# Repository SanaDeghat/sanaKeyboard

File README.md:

# sanaKeyboard
What?
Its (then pcb of) my own custom keyboard. its a wireless split keyboard (in theory) that uses nice nano! 

Why?
So I havwe this firend who rly liked hardware and keeps talkign about it, plus i kinda bacame a stasis sidekick so i figured i should prob learn how to do hardware given that im like guiding ppl in it. That + I keep seeing vdieos of ppl going click click click on their fancy ahh mechanical keyboard and i cant efford that so i figured i make my own, that said im not printing it this was kind of my firs time so ill make a better one next time and make that one!!!!

How?
I used keycad and urgogen! for more details pls go to my journal! 

Live demo: 
Im ngl idk how to live demo this so ill just put some pics here (i drew the fox myself int he the cutest) : 

What you struggled with and what you learned?
I cried istg from things not connecting it looked like pasta from hwo messy it was (look at my commits and journal for more info) but lowky i mifht be in the cult now it was kinda fun connecting everyhting (and thank you kai for helping me)

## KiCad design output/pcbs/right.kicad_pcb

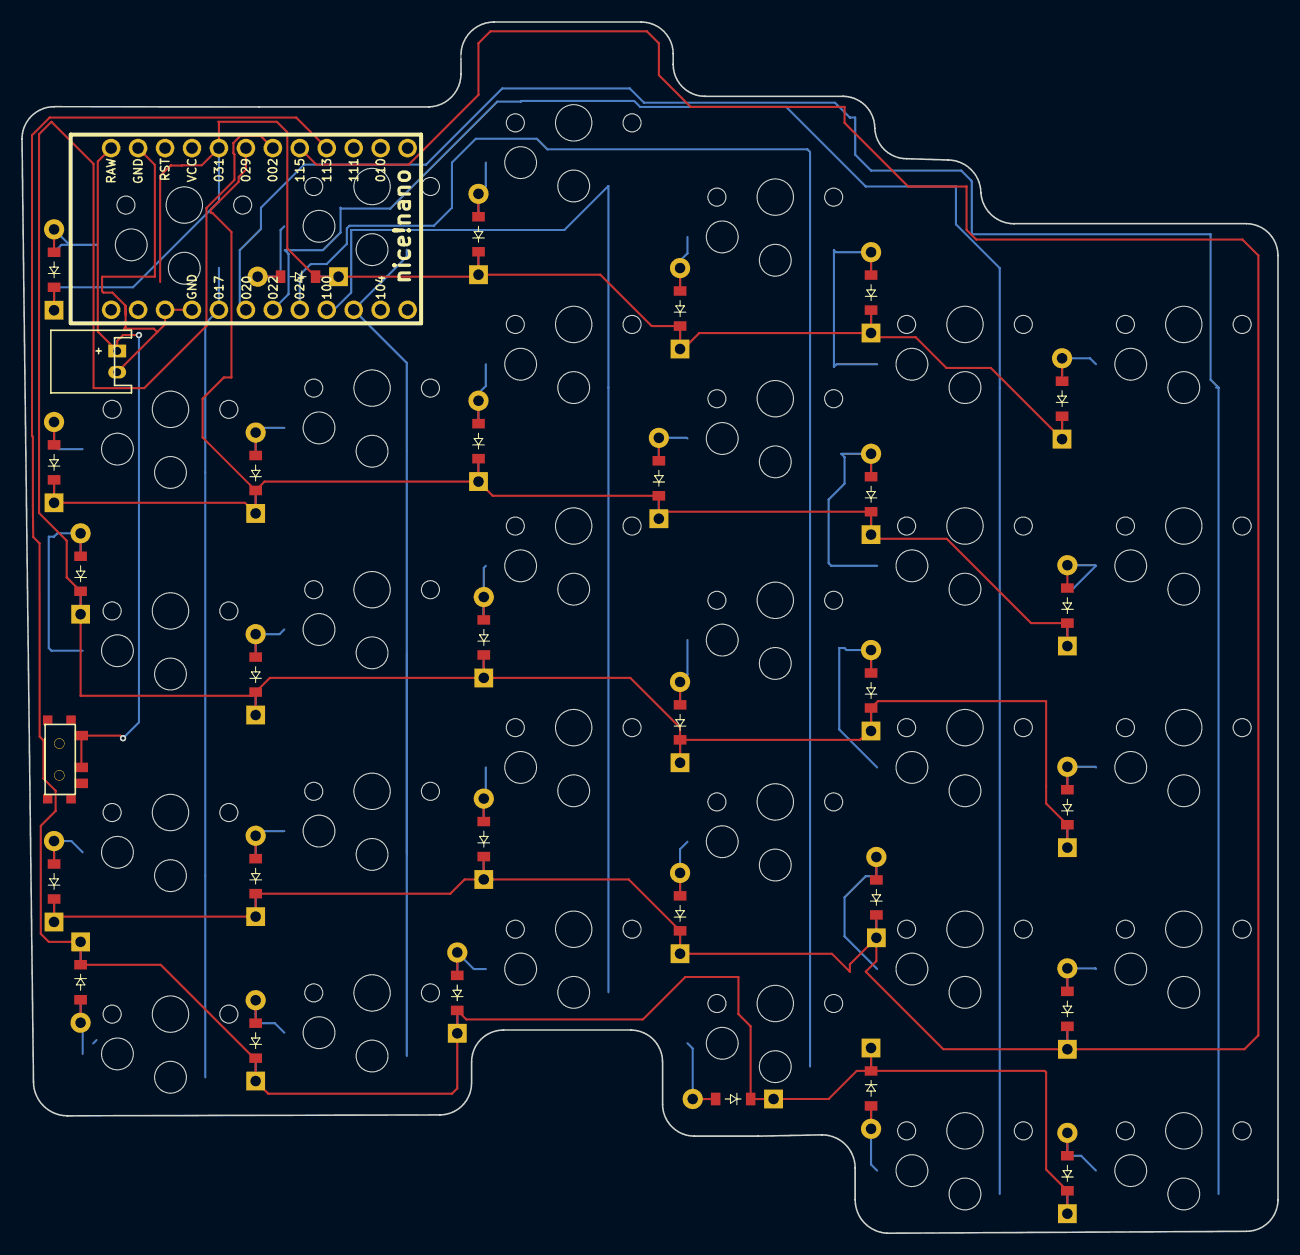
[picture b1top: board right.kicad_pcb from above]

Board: 2 copper layers, 118.4 x 114.2 mm, 63 parts (0 on the bottom side), 43 nets.

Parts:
D1, D2, D3, D4, D5, D6, D7, D8, D9, D10, D11, D12, D13, D14, D15, D16, D17, D18, D19, D20, D21, D22, D23, D24, D25, D26, D27, D28, D29, D30: ComboDiode
JST1: JST_PH_S2B-PH-K_02x2.00mm_Angled
MCU1: nice_nano
S1, S2, S3, S4, S5, S6, S7, S8, S9, S10, S11, S12, S13, S14, S15, S16, S17, S18, S19, S20, S21, S22, S23, S24, S25, S26, S27, S28, S29, S30: PG1350
T1: SPDT_C128955

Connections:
GND: JST1.2, MCU1.3, MCU1.4, MCU1.23
P002: D3.1, D8.1, D13.1, D18.1, D23.1, D28.1, MCU1.18
P011: MCU1.10, S21.1, S22.1, S23.1, S24.1, S25.1
P017: MCU1.5, S26.1, S27.1, S28.1, S29.1, S30.1
P020: MCU1.6, S1.1, S2.1, S3.1, S4.1, S5.1
P022: MCU1.7, S6.1, S7.1, S8.1, S9.1, S10.1
P024: MCU1.8, S11.1, S12.1, S13.1, S14.1, S15.1
P029: D4.1, D9.1, D14.1, D19.1, D24.1, D29.1, MCU1.19
P031: D5.1, D10.1, D15.1, D20.1, D25.1, D30.1, MCU1.20
P100: MCU1.9, S16.1, S17.1, S18.1, S19.1, S20.1
P113: D1.1, D6.1, D11.1, D16.1, D21.1, D26.1, MCU1.16
P115: D2.1, D7.1, D12.1, D17.1, D22.1, D27.1, MCU1.17
RAW: JST1.1, MCU1.24, T1.1, T1.2
index_bottom: D22.2, S22.2
index_home: D23.2, S23.2
index_mod: D25.2, S25.2
index_num: D21.2, S21.2
index_top: D24.2, S24.2
inner_bottom: D27.2, S27.2
inner_home: D28.2, S28.2
inner_mod: D30.2, S30.2
inner_num: D26.2, S26.2
inner_top: D29.2, S29.2
middle_bottom: D17.2, S17.2
middle_home: D18.2, S18.2
middle_mod: D20.2, S20.2
middle_num: D16.2, S16.2
middle_top: D19.2, S19.2
outer_bottom: D2.2, S2.2
outer_home: D3.2, S3.2
outer_mod: D5.2, S5.2
outer_num: D1.2, S1.2
outer_top: D4.2, S4.2
pinky_bottom: D7.2, S7.2
pinky_home: D8.2, S8.2
pinky_mod: D10.2, S10.2
pinky_num: D6.2, S6.2
pinky_top: D9.2, S9.2
ring_bottom: D12.2, S12.2
ring_home: D13.2, S13.2
ring_mod: D15.2, S15.2
ring_num: D11.2, S11.2
ring_top: D14.2, S14.2

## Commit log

2026-03-18 sorry ilost track of time, just trying to fix the PCB
2026-03-19 makign a rtight kicad maybe
2026-03-20 right side is alsmost finished
2026-03-20 ITS FINISHED ALL THE DNC AHHHHHHHHH
2026-03-20 I THINK ITS DONE
2026-03-21 FINAL SILK SCREEN ADDED
2026-03-21 Fixing my readme so it gets apprioved (hopefully)
2026-03-21 Create journal.md with image entries
    Added journal entries with images.
2026-03-21 Ive been told i need BOM lol
2026-03-21 more silkscreen attempts
